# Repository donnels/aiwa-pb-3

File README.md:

# aiwa-pb-3
Alternatives for an Aiwa PB-3 lead acid battery

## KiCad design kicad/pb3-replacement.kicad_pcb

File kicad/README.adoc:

= Circuit Design & Emulation
ifndef::flag-book[]
:toc: right
:toclevels: 5
:sectnums:
:sectnumlevels: 5
endif::[]
ifdef::flag-book[]
:imagesdir-save: {imagesdir}
:imagesdir: kicad
endif::[]

`pb3-replacement.kicad_pro` (with its `.kicad_sch`/`.kicad_pcb`) is the
living electrical design for the replacement pack: a 68×17.8×8mm board that
takes USB-C 5V in and delivers a regulated 2.0-2.4V deck rail from a 1S
LiPo cell.

== Component Selection

Each part below was picked from the candidates surveyed in
`research/README.adoc`, chosen for SOT-23-6 footprints (small enough for
the enclosure) and for matching the behavior already proven on the clone
teardown boards.

CN3058E (charger)::
Linear Li-ion/LiPo charge management IC. Takes the USB-C 5V rail, applies
CC/CV charging to the cell, and needs only a handful of external passives
— important with almost no board area to spare.

DW01A + FS8205A (protection)::
Discrete battery management system on the cell tabs. DW01A senses cell
voltage and current; FS8205A is the dual N-MOSFET it drives to cut the
path on overvoltage, undervoltage, or overcurrent/short. Chosen instead of
trusting the charger or buck stage alone, so a fault anywhere downstream
still leaves the cell protected.

Buck regulator (TPS61023-class)::
Steps the ~3.7V cell rail down to the 2.0-2.4V the deck expects. The
feedback resistor sets the output: 100kΩ gives the PB-S5 clone's default
2.4V; the forum's 120kΩ swap gives 2.1V. Extrapolating those two points
puts 2.0V at roughly 130kΩ — an unverified estimate, not a datasheet
value. `pb3-architecture-sizing.cir` models 2.0V directly; confirm the
real resistor against the vendor datasheet and bench measurement before
fabrication.

OVP clamp (Zener/TVS)::
Added on top of what the clone boards do: clamps the output below 3V if
the buck stage fails, so the deck never sees the raw 3.7V cell rail.

== Circuit Emulation

Emulation happens in two stages so a passing simulation always means
something about the *real* board, not just about an idealized stand-in.
See `pb3-notes.adoc`'s "Verification Chain" for how this fits the
project's broader print/fit/design/verify sequence.

=== Stage 1 — Architecture Sizing (exploratory, not a verification)

`pb3-architecture-sizing.cir` is a system-level ngspice model used to
pick topology and nominal values *before* the schematic below existed.
It approximates the CN3058E charger, 1S LiPo, DW01A/FS8205A protection,
2.0V buck regulator, 200mA deck load, and output clamp with behavioral
sources (idealized voltages/thresholds, not real part models). It is
useful for checking operating points and assumptions. It does **not**
validate the real IC compensation network, stability, thermal behavior,
the unverified AIWA connector pinout, or — critically — the actual
schematic/PCB below: the netlist is hand-written, independent of
`pb3-replacement.kicad_sch`, so a passing run only proves the idealized
model is self-consistent.

Run it with ngspice:

[source,bash]
----
ngspice -b -o pb3-architecture-sizing.log pb3-architecture-sizing.cir
grep -E 'vout_|load_current|vbat' pb3-architecture-sizing.log
----

Expected results: ~1.98V at the deck output, 198mA load current, 3.7V
at the idealized cell. The model hard-codes a 2.0V buck target — it
does not use the ~130kΩ feedback-resistor estimate above, which is for
the real IC's feedback divider, not this behavioral model.

=== Stage 2 — Schematic-Derived Simulation (netlist export unblocked; full SPICE sim still partial)

The step that actually verifies the design generates a SPICE netlist
*from* `pb3-replacement.kicad_sch` (`kicad-cli sch export netlist
--format spice`) and simulates it with real or vendor-published SPICE
models for `U1` (TP4056), `U2` (DW01A), `Q1` (FS8205A substitute, see
below), `U3` (TPS62200), and `D1` (Zener) wherever such models exist.
That checks the same reference designators and values that get
fabricated, closing the gap that Stage 1 leaves open.

`pb3-replacement.kicad_sch` is now a real, pin-wired schematic instead of
a block/documentation diagram: every component is a real KiCad library
symbol (embedded in `lib_symbols`), and every pin is tied to its net via a
same-named global label placed at the pin, reusing the exact net names
already routed on the PCB (`VBUS`, `VBAT`, `VBAT_RAW_NEG`, `GND`,
`OD`/`OC`) plus new nets for the passives the PCB was missing (see "PCB
Routing" below). `kicad-cli sch erc` on this schematic reports **0
errors** (down from 19 dangling/unconnected errors on the old block
diagram); the remaining ~40 warnings are expected/documented — footprint
library-table warnings from running outside a configured KiCad project,
`NC_*` single-pin nets that are intentionally left dangling (documented
below), and off-grid cosmetic placements from the label-per-pin layout
strategy.

Three of the schematic's original `lib_id`s did not just lack wiring —
they were **unresolvable against real KiCad libraries** and would have
failed to open cleanly in KiCad at all. They were corrected to real,
pin-compatible library parts:

* `Battery_Management:TP4056` → `Battery_Management:TP4056-42-ESOP8`
  (same SOIC-8 pinout already used for PCB routing).
* `Regulator_Switching:TPS62200` → `Regulator_Switching:TPS62200DBV`
  (same SOT-23-5 pinout already used for PCB routing).
* `Connector:USB_C_Receptacle_USB2.0` → `Connector:USB_C_Receptacle_PowerOnly_6P`
  (matches the existing 6-pad `GCT_USB4105-xx-A` footprint already
  placed on the PCB; note the CC1/CC2 pins are wired to `NC_CC1`/`NC_CC2`
  — proper USB-C power-only negotiation needs 5.1kΩ pull-downs on both,
  which this revision does not add — a newly-discovered, real gap,
  documented here rather than fixed silently).
* `Transistor_FET:FS8205A` does not exist in any public KiCad library.
  `Transistor_FET:DMG9926UDM` (a real Diodes Inc. common-drain dual
  N-MOSFET, SOT-23-6) is used as a documented substitute: its pin
  numbering (1=D1, 2/5=common S1/D2, 3=S2, 4=G2, 6=G1) maps pin-for-pin
  onto the FS8205A pinout already cited in "PCB Routing" below. This is a
  schematic-symbol substitution for simulation/ERC purposes only — it
  does not change which part is fabricated.

Exporting the netlist now succeeds structurally
(`kicad-cli sch export netlist --format spice`), where it previously had
nothing valid to export. It is **still not a fully simulatable SPICE
netlist**: `kicad-cli`'s built-in SPICE exporter only resolves passives
(`R`/`L`/`C`) by reference-designator convention; multi-pin parts
(`U1`/`U2`/`Q1`/`U3`/diodes/connectors) need `Sim.Device`/`Sim.Pins`/
`Sim.Model` fields added per-symbol before ngspice can use them, and two
of those parts have no public SPICE model to attach in the first place
(DW01A, FS8205A/DMG9926UDM) — the same documented gap Stage 1 already
calls out. Adding those Spice fields for the parts that do have public
models (TPS62200, and third-party TP4056 models) is the concrete next
step to get from "netlist exports" to "netlist simulates."

Verify with vendor SPICE models and bench measurements before connecting
an AIWA deck. This is the electrical half of the compliance check; the
mechanical half is the OpenSCAD fit check.

=== Interactive Exploration & Physical POC Loop

CI only ever runs `ngspice -b` (batch mode): fixed inputs in, a log file
out, useful for a pass/fail gate but not for poking at the circuit. Use
an interactive ngspice session to explore *before* trusting a number:

[source,bash]
----
docker run --rm -it -v "$PWD/kicad":/work -w /work --entrypoint ngspice \
  aiwa-pb3-ngspice pb3-architecture-sizing.cir
----

At the `ngspice>` prompt:

* `run` — execute the `.tran` analysis already in the file.
* `plot v(vout) v(bat) v(bms)` — waveform the deck output, cell, and
  protected-rail nodes against each other.
* `alter vbat = 3.5` / `alter rload = 20` then `rerun` — sweep a
  parameter (end-of-discharge cell voltage, heavier deck load) without
  editing the file and re-running batch.
* `iplot vout` before `run` — live-updating plot while the transient
  computes, useful for long sweeps.

This is where the model's idealizations get tested on purpose: try to
`alter` the OVP/UV thresholds in `pb3-architecture-sizing.cir` to
something that should visibly fail and see if the behavioral `B` sources
even react with a realistic shape (delay, ringing, hysteresis) or just
snap instantly. A too-clean reaction is the signal that a part is not
meaningfully simulated yet — currently true for the DW01A/FS8205A
trip behavior and the TPS62200 loop response (see the model's own
comments).

**Graphical tools for exploring the circuit:**

* *ngspice's own plotting* — if built with X11/Qt support (the Debian
  `ngspice` package used by `containers/ngspice/Dockerfile` is), `plot`/
  `iplot` open native graph windows. Run the container with `-it` and
  forward the display (`-e DISPLAY=$DISPLAY -v /tmp/.X11-unix:/tmp/.X11-unix`
  on Linux) instead of running headless.
* *Xschem + ngspice* — free schematic-capture front end that drives
  ngspice directly: draw the circuit, click a wire/pin to place a probe,
  hit simulate, see the waveform in the same window. Good for exploring
  the TP4056/DW01A/FS8205A/TPS62200 topology graphically without waiting
  on Stage 2's KiCad netlist export.
* *QUCS-S* — schematic capture with ngspice as its simulation backend
  and a built-in interactive waveform viewer; another schematic-first
  alternative to hand-editing `.cir` files.
* *KiCad's own "Simulate" tab* (eeschem, ngspice-integrated) — click a
  net on the schematic to probe it interactively. The schematic now has
  real pin-to-pin wiring (see Stage 2 above), so this is usable for
  probing net connectivity; full transient simulation in this tab still
  needs the same per-symbol Spice model fields called out in Stage 2.

**Turning an exploration finding into a physical POC:** when interactive
exploration flags a node ngspice can't be trusted for — DW01A/FS8205A
trip voltage and timing, TPS62200 transient response under a real deck
load step, the Zener/TVS clamp's actual knee — build the smallest
dead-bug/breadboard rig that isolates just that question, using the real
part: bench supply standing in for the cell, a scope on the node in
doubt, a load step or ramp matching what the deck actually does. Measure
it, then fold the number back into `pb3-architecture-sizing.cir` (replace
the idealized threshold/step in the relevant `B` source) with a comment
citing the POC measurement, so the next simulation run reflects reality
instead of an assumption. See `pb3-notes.adoc`'s "Verification Chain" for
where this loop sits relative to Stage 1/Stage 2/bench test.

== PCB Routing

`pb3-replacement.kicad_pcb` places footprints for the 1S protection/buck
power path (`J1` USB-C, `U1` TP4056 charger, `U2` DW01A protection IC,
`Q1` FS8205A dual-FET, `U3` buck regulator, `J2` deck connector, `BT1`
LiPo cell). `pb3-replacement.kicad_sch` is now a real, pin-wired
schematic (see "Circuit Emulation" → Stage 2 above) that documents the
same pinouts used for PCB routing below, so this section and the
schematic no longer disagree with each other. Nets and copper traces on
the PCB were still added directly (not derived from the schematic, since
KiCad's PCB-from-schematic re-annotation was not run this pass) using
verified, datasheet-cited pinouts for the actual parts placed on the
board:

* TP4056 (SOIC-8): 1=TEMP, 2=PROG, 3=GND, 4=VCC, 5=BAT, 6=~STDBY, 7=~CHRG, 8=CE.
* DW01A (SOT-23-6): 1=OD, 2=CS, 3=OC, 4=TD, 5=VCC, 6=GND — cross-checked
  against Fortune Semiconductor datasheet DW01A-DS-12_EN Rev 1.2, Section 6.
* FS8205A (SOT-23-6): 1=S1, 2/5=D12 (common drain), 3=S2, 4=G2, 6=G1. The
  schematic's `Q1` symbol is `DMG9926UDM` (documented substitute, see
  Stage 2 above) with the same pin mapping.
* TPS62200DBV (SOT-23-5): 1=VIN, 2=GND, 3=EN, 4=FB, 5=SW. The PCB
  footprint is labelled `TPS61023`, but the real TI TPS61023 is a 6-pin
  SOT-563 part that doesn't match this board's 5-pad SOT-23-5 footprint.
  The schematic's actual symbol for `U3` is `Regulator_Switching:TPS62200DBV`
  (a real SOT-23-5 buck), so the TPS62200 pinout was used to route the 5
  pads that exist — the footprint name is a pre-existing naming
  inconsistency in the repo, left unchanged.

Routed nets: `VBUS`, `GND` (includes TEMP/CE tied low and the
DW01A/FS8205A current-sense node), `VBAT` (cell/protected-positive rail,
includes `EN` tied high for an always-on regulator), `VBAT_RAW_NEG`
(raw/unprotected cell negative — kept separate from `GND` so the
protection circuit still does its job), and the DW01A→FS8205A gate
signals `OD`/`OC`.

Several pins are still left as single-pad, unrouted `NC_*` nets on the
**PCB** (`NC_PROG`, `NC_STDBY`, `NC_CHRG`, `NC_TD`, `NC_FB`, `NC_SW`,
`NC_VOUT`) because the passives their function depends on — the PROG
resistor (`R2`), charger status LEDs (`D2`/`D3`) with their current-limit
resistors (`R3`/`R4`), the buck's inductor (`L1`), the FB feedback
divider's second resistor (`R5`), and the output capacitor (`C1`) — have
footprints in the schematic now (used for Stage 2 netlist export) but
**not yet as PCB footprints/copper on this tight 68×17.8mm board**.
`kibot.yaml`'s `ignore_unconnected` preflight option keeps DRC clean
despite this. Placing and routing those 6 new footprints (`R2`-`R5`,
`L1`, `C1`, plus `D2`/`D3` LEDs) is the concrete next task to close this
gap — precisely scoped now that the schematic fixes their values and net
names, but not attempted in this pass given the board's limited area.

Component values chosen for the schematic (flagged by confidence level,
not asserted as final):

* `R2` (PROG) = 2.4kΩ — derived from the TP4056 datasheet formula
  `Ichg(mA) = 1200/Rprog(kΩ)` for a 500mA charge target.
* `L1` = 2.2µH — taken directly from `pb3-notes.adoc`'s existing
  Electrical Block Requirements.
* `R3`/`R4` (LED current-limit) = 1kΩ — generic placeholder, **not
  verified** against the LED's actual forward-current spec.
* `R5` (FB divider bottom resistor) = **TBD** — left unset; the TI
  TPS62200 datasheet was not reachable this session to derive it from
  `R1`'s ~130kΩ estimate above using the real feedback-voltage formula.
* `C1` (buck output cap) = 10µF — generic typical value, **not verified**
  against the TPS62200 datasheet's stability requirements.

This is a best-effort prototype routing based on standard reference-design
pinouts, not a verified production layout — confirm every net against the
real datasheets and bench-test before fabrication, same as the existing
disclaimers on connector pinout and the feedback resistor value above.

== 3D Exports & Renders

Alongside the fabrication outputs (gerbers, drill, position files),
`kicad-cli` (KiCad 9, `pcb export`/`pcb render`) produces:

* `pb3-replacement.step` — STEP solid model, for any MCAD tool.
* `pb3-replacement.glb` — binary glTF, converted to
  `results/cad/pb3-replacement-board.stl` by the `containers/trimesh`
  container (rescale, re-axis, re-origin — see its README).
* `pb3-replacement-render-top.png` / `-render-iso.png` — photorealistic
  raytraced renders of the finished board.

.Isometric render of the replacement board
image::pb3-replacement-render-iso.png[]

The STL feeds `openscad/pb3-fit-check.scad` — see "Mechanical Design
(OpenSCAD)" for the fit-check render.

== Free Training & Docs

* https://github.com/KiCad/kicad-source-mirror[KiCad source (GitHub mirror)] —
  official KiCad source code; the repository README links to the free
  documentation site.
* https://github.com/joanbono/awesome-kicad[awesome-kicad] — curated list
  of free KiCad tutorials, plugins, and libraries.
* https://github.com/ngspice/ngspice[ngspice] — official circuit
  simulator source and documentation used by "Circuit Emulation" above.
* https://github.com/kitspace/awesome-electronics[awesome-electronics] —
  curated list of free datasheets, application notes, and component
  selection references, useful background for "Component Selection".
* https://github.com/KhronosGroup/glTF[glTF specification] — the format
  behind the `.glb` export used for the mechanical fit-check.

//END OF DOC
ifdef::flag-book[]
:imagesdir: {imagesdir-save}
endif::[]

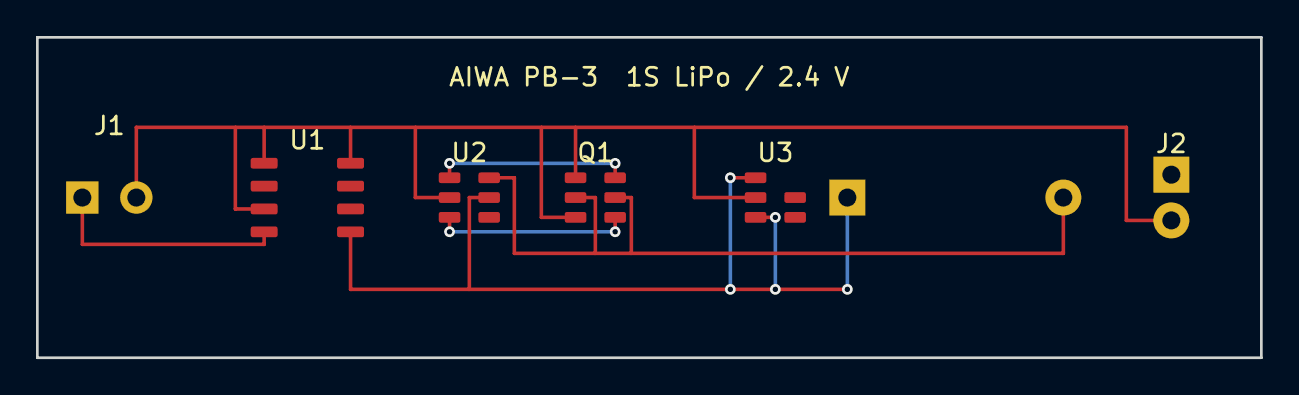
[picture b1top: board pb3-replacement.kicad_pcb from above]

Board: 2 copper layers, 68.0 x 17.8 mm, 7 parts (1 on the bottom side), 6 nets.

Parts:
BT1: LiPo_3.7V_500-1500mAh; PB3_LIPO_68x17.8mm
J1: USB_C_5V_IN; PB3_USB_C
J2: AIWA_DECK_2.4V; PB3_DECK_CONNECTOR
Q1: FS8205A; PB3_FS8205A_SOT23-6
U1: TP4056; PB3_TP4056_SOIC8
U2: DW01A; PB3_DW01A_SOT23-6
U3: TPS61023_2.4V; PB3_TPS61023_SOT23-5

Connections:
GND: J1.2, J2.2, Q1.1, Q1.3, U1.1, U1.3, U1.8, U2.2, U3.2
OC: Q1.4, U2.3
OD: Q1.6, U2.1
VBAT: BT1.1, U1.5, U2.5, U3.1, U3.3
VBAT_RAW_NEG: BT1.2, Q1.2, Q1.5, U2.6
VBUS: J1.1, U1.4

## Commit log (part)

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2025-12-11 photos
2025-12-11 first rough draft
2025-12-11 next test
2025-12-11 ci: refresh CAD outputs
2025-12-11 test
2025-12-11 now lets pipe that rough draft through the ci cd pipe
2025-12-11 nike
2025-12-11 hmmm
2025-12-11 ci: refresh outputs
2025-12-11 pre cleanup
2025-12-11 cleanup
2025-12-12 test after documenting why we are doing stuff this way.
2025-12-12 ci: refresh outputs [skip ci]
2025-12-12 more structure
2025-12-12 ajskhdgjhkasdgfjhkasgfhkj
2025-12-12 some restructuring to make it more modular
2025-12-12 further restructure
2025-12-12 when did this abscond?
2025-12-12 trigger
2025-12-12 test new actions
2025-12-12 debug added
2025-12-12 ci: plantuml renders [skip ci]
2025-12-12 one push is all it takes
2025-12-12 ci: render all outputs [skip ci]
2025-12-13 test with hellor world
2025-12-13 Trigger build
2025-12-13 retest with -s all
